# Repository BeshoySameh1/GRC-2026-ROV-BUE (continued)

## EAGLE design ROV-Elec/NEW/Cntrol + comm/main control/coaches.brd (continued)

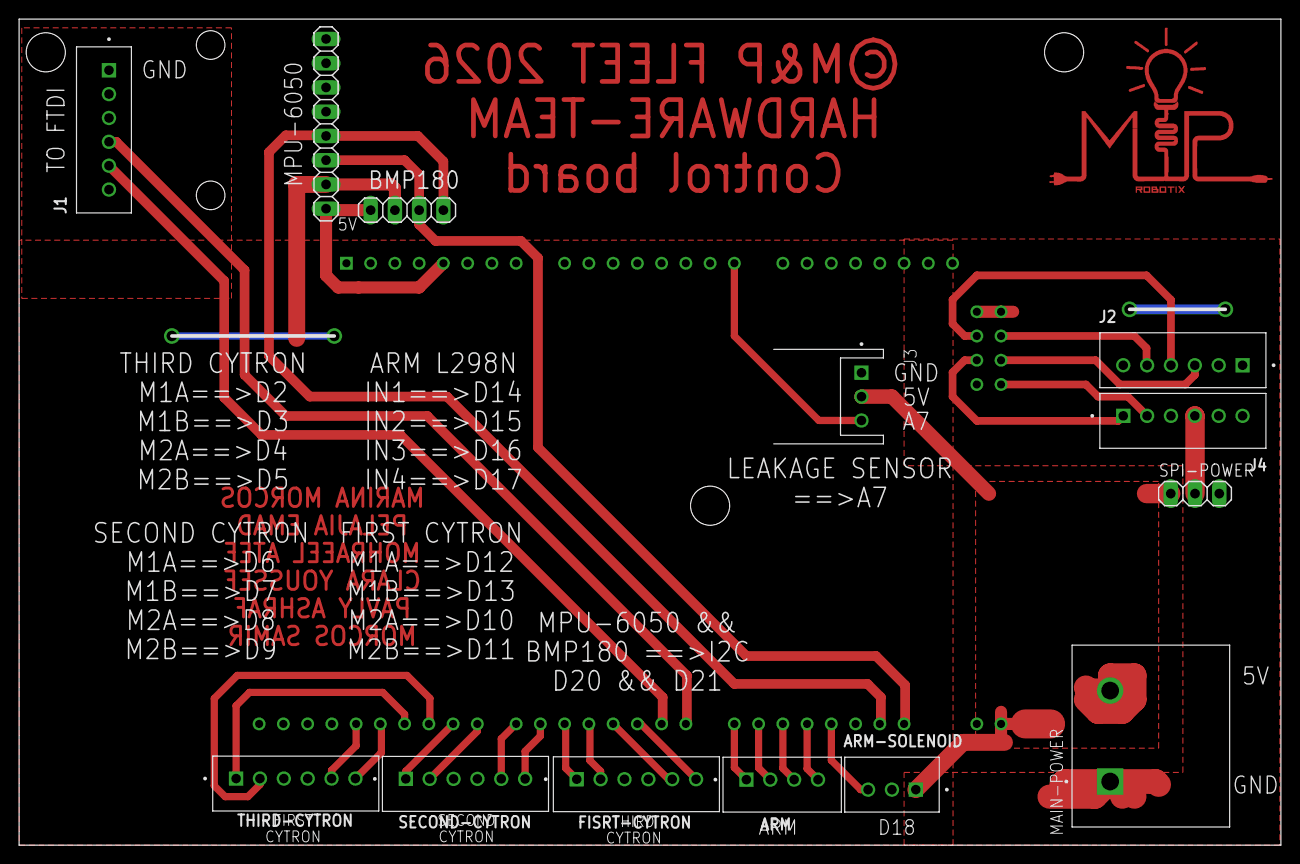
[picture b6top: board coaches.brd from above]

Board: 2 copper layers, 132.2 x 86.5 mm, 14 parts (1 on the bottom side), 31 nets.
